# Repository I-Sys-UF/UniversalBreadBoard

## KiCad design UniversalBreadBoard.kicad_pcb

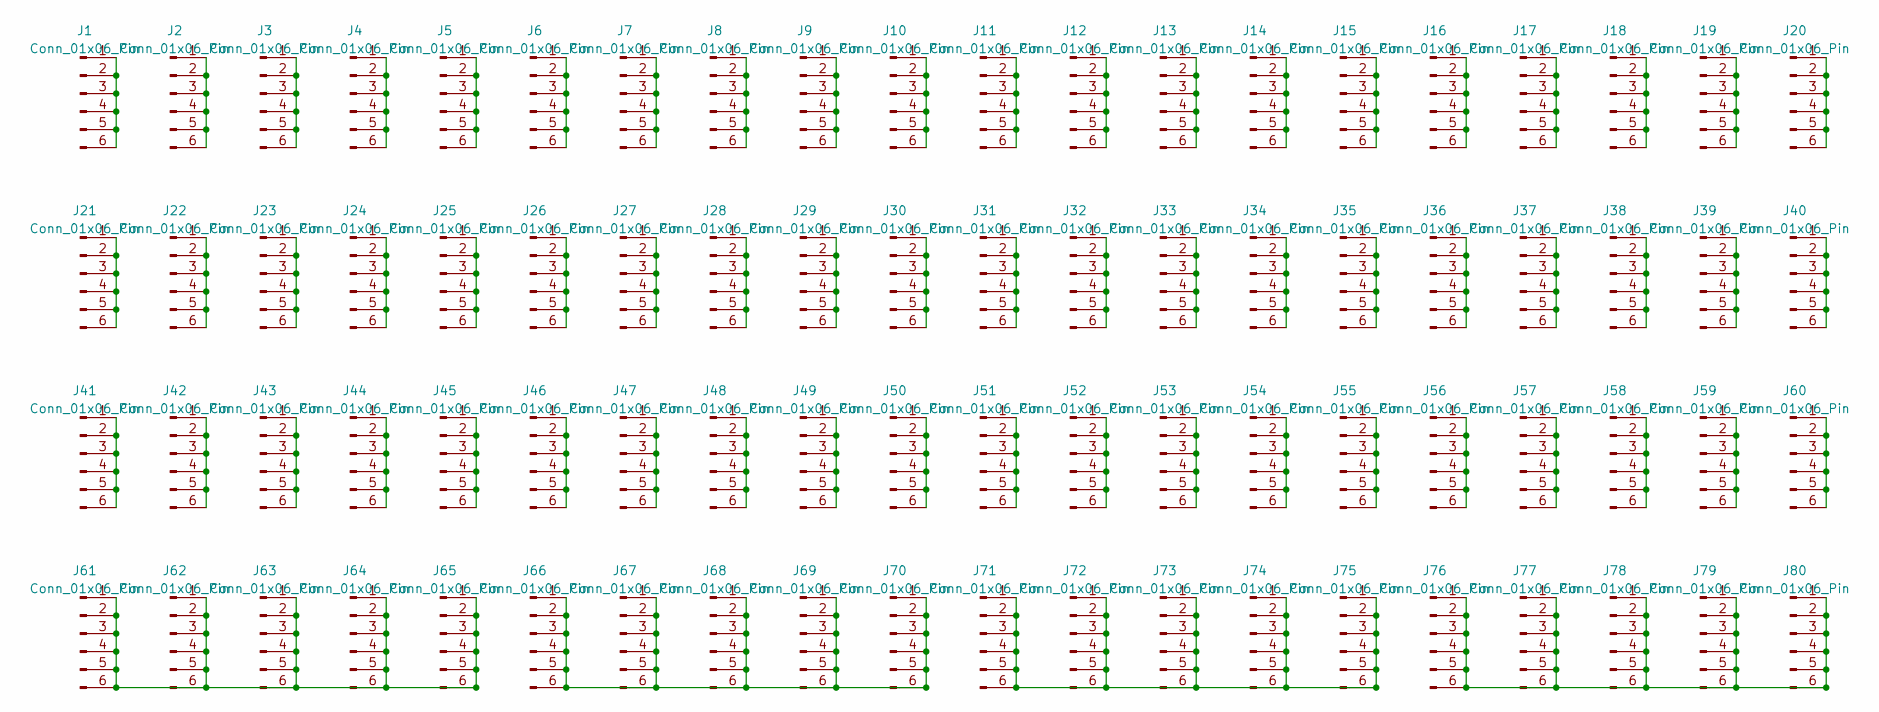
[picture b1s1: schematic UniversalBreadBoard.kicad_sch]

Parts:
J1, J2, J3, J4, J5, J6, J7, J8, J9, J10, J11, J12, J13, J14, J15, J16, J17, J18, J19, J20, J21, J22, J23, J24, J25, J26, J27, J28, J29, J30, J31, J32, J33, J34, J35, J36, J37, J38, J39, J40, J41, J42, J43, J44, J45, J46, J47, J48, J49, J50, J51, J52, J53, J54, J55, J56, J57, J58, J59, J60, J61, J62, J63, J64, J65, J66, J67, J68, J69, J70, J71, J72, J73, J74, J75, J76, J77, J78, J79, J80: Conn_01x06_Pin; Pins

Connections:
unnamed: J1.1, J1.2, J1.3, J1.4, J1.5, J1.6
unnamed: J2.1, J2.2, J2.3, J2.4, J2.5, J2.6
unnamed: J3.1, J3.2, J3.3, J3.4, J3.5, J3.6
unnamed: J4.1, J4.2, J4.3, J4.4, J4.5, J4.6
unnamed: J5.1, J5.2, J5.3, J5.4, J5.5, J5.6
unnamed: J6.1, J6.2, J6.3, J6.4, J6.5, J6.6
unnamed: J7.1, J7.2, J7.3, J7.4, J7.5, J7.6
unnamed: J8.1, J8.2, J8.3, J8.4, J8.5, J8.6
unnamed: J9.1, J9.2, J9.3, J9.4, J9.5, J9.6
unnamed: J10.1, J10.2, J10.3, J10.4, J10.5, J10.6
unnamed: J11.1, J11.2, J11.3, J11.4, J11.5, J11.6
unnamed: J12.1, J12.2, J12.3, J12.4, J12.5, J12.6
unnamed: J13.1, J13.2, J13.3, J13.4, J13.5, J13.6
unnamed: J14.1, J14.2, J14.3, J14.4, J14.5, J14.6
unnamed: J15.1, J15.2, J15.3, J15.4, J15.5, J15.6
unnamed: J16.1, J16.2, J16.3, J16.4, J16.5, J16.6
unnamed: J17.1, J17.2, J17.3, J17.4, J17.5, J17.6
unnamed: J18.1, J18.2, J18.3, J18.4, J18.5, J18.6
unnamed: J19.1, J19.2, J19.3, J19.4, J19.5, J19.6
unnamed: J20.1, J20.2, J20.3, J20.4, J20.5, J20.6
unnamed: J21.1, J21.2, J21.3, J21.4, J21.5, J21.6
unnamed: J22.1, J22.2, J22.3, J22.4, J22.5, J22.6
unnamed: J23.1, J23.2, J23.3, J23.4, J23.5, J23.6
unnamed: J24.1, J24.2, J24.3, J24.4, J24.5, J24.6
unnamed: J25.1, J25.2, J25.3, J25.4, J25.5, J25.6
unnamed: J26.1, J26.2, J26.3, J26.4, J26.5, J26.6
unnamed: J27.1, J27.2, J27.3, J27.4, J27.5, J27.6
unnamed: J28.1, J28.2, J28.3, J28.4, J28.5, J28.6
unnamed: J29.1, J29.2, J29.3, J29.4, J29.5, J29.6
unnamed: J30.1, J30.2, J30.3, J30.4, J30.5, J30.6
unnamed: J31.1, J31.2, J31.3, J31.4, J31.5, J31.6
unnamed: J32.1, J32.2, J32.3, J32.4, J32.5, J32.6
unnamed: J33.1, J33.2, J33.3, J33.4, J33.5, J33.6
unnamed: J34.1, J34.2, J34.3, J34.4, J34.5, J34.6
unnamed: J35.1, J35.2, J35.3, J35.4, J35.5, J35.6
unnamed: J36.1, J36.2, J36.3, J36.4, J36.5, J36.6
unnamed: J37.1, J37.2, J37.3, J37.4, J37.5, J37.6
unnamed: J38.1, J38.2, J38.3, J38.4, J38.5, J38.6
unnamed: J39.1, J39.2, J39.3, J39.4, J39.5, J39.6
unnamed: J40.1, J40.2, J40.3, J40.4, J40.5, J40.6
unnamed: J41.1, J41.2, J41.3, J41.4, J41.5, J41.6
unnamed: J42.1, J42.2, J42.3, J42.4, J42.5, J42.6
unnamed: J43.1, J43.2, J43.3, J43.4, J43.5, J43.6
unnamed: J44.1, J44.2, J44.3, J44.4, J44.5, J44.6
unnamed: J45.1, J45.2, J45.3, J45.4, J45.5, J45.6
unnamed: J46.1, J46.2, J46.3, J46.4, J46.5, J46.6
unnamed: J47.1, J47.2, J47.3, J47.4, J47.5, J47.6
unnamed: J48.1, J48.2, J48.3, J48.4, J48.5, J48.6
unnamed: J49.1, J49.2, J49.3, J49.4, J49.5, J49.6
unnamed: J50.1, J50.2, J50.3, J50.4, J50.5, J50.6
unnamed: J51.1, J51.2, J51.3, J51.4, J51.5, J51.6
unnamed: J52.1, J52.2, J52.3, J52.4, J52.5, J52.6
unnamed: J53.1, J53.2, J53.3, J53.4, J53.5, J53.6
unnamed: J54.1, J54.2, J54.3, J54.4, J54.5, J54.6
unnamed: J55.1, J55.2, J55.3, J55.4, J55.5, J55.6
unnamed: J56.1, J56.2, J56.3, J56.4, J56.5, J56.6
unnamed: J57.1, J57.2, J57.3, J57.4, J57.5, J57.6
unnamed: J58.1, J58.2, J58.3, J58.4, J58.5, J58.6
unnamed: J59.1, J59.2, J59.3, J59.4, J59.5, J59.6
unnamed: J60.1, J60.2, J60.3, J60.4, J60.5, J60.6
unnamed: J61.1, J61.2, J61.3, J61.4, J61.5, J61.6, J62.1, J62.2, J62.3, J62.4, J62.5, J62.6, J63.1, J63.2, J63.3, J63.4, J63.5, J63.6, J64.1, J64.2, J64.3, J64.4, J64.5, J64.6, J65.1, J65.2, J65.3, J65.4, J65.5, J65.6
unnamed: J66.1, J66.2, J66.3, J66.4, J66.5, J66.6, J67.1, J67.2, J67.3, J67.4, J67.5, J67.6, J68.1, J68.2, J68.3, J68.4, J68.5, J68.6, J69.1, J69.2, J69.3, J69.4, J69.5, J69.6, J70.1, J70.2, J70.3, J70.4, J70.5, J70.6
unnamed: J71.1, J71.2, J71.3, J71.4, J71.5, J71.6, J72.1, J72.2, J72.3, J72.4, J72.5, J72.6, J73.1, J73.2, J73.3, J73.4, J73.5, J73.6, J74.1, J74.2, J74.3, J74.4, J74.5, J74.6, J75.1, J75.2, J75.3, J75.4, J75.5, J75.6
unnamed: J76.1, J76.2, J76.3, J76.4, J76.5, J76.6, J77.1, J77.2, J77.3, J77.4, J77.5, J77.6, J78.1, J78.2, J78.3, J78.4, J78.5, J78.6, J79.1, J79.2, J79.3, J79.4, J79.5, J79.6, J80.1, J80.2, J80.3, J80.4, J80.5, J80.6

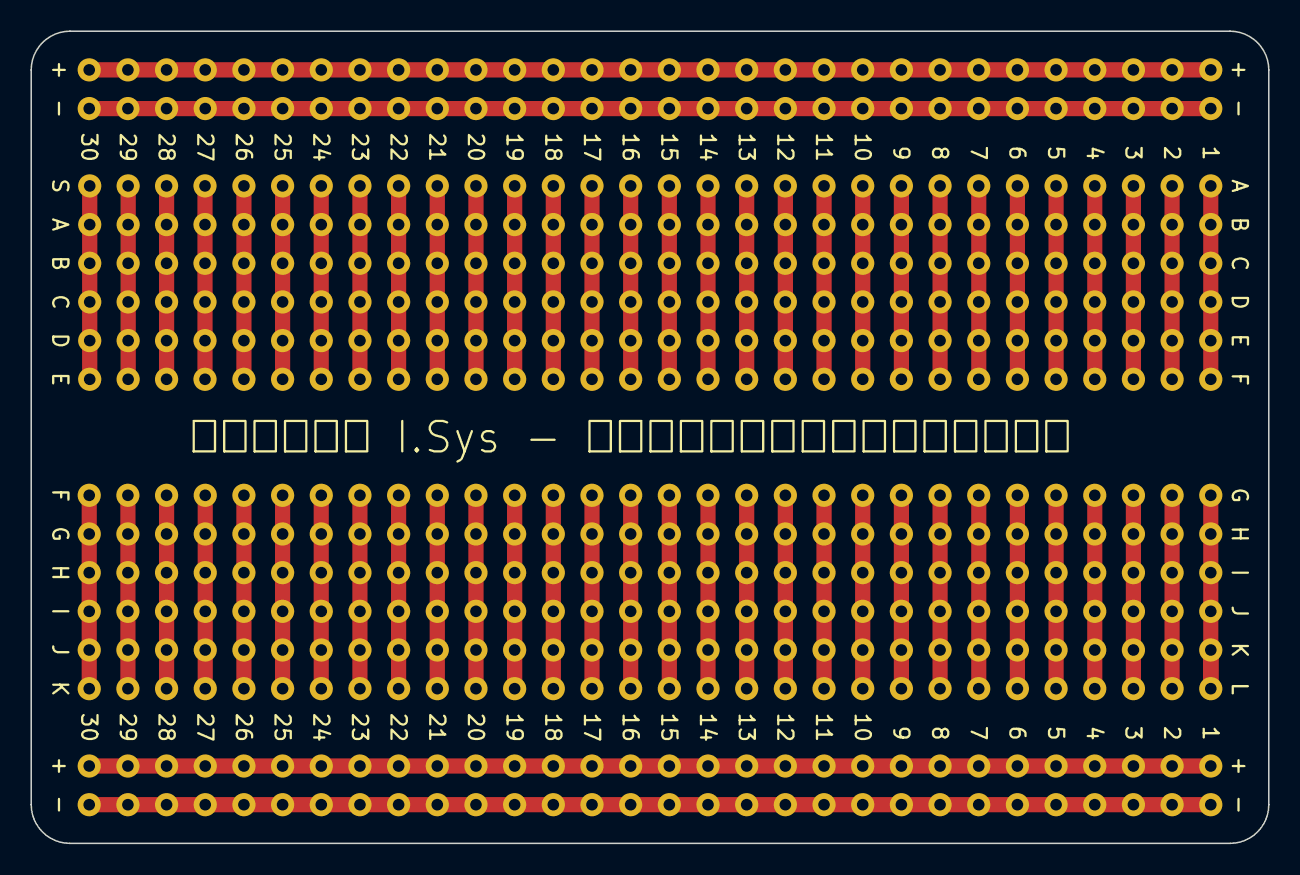
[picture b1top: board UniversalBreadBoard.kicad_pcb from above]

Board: 2 copper layers, 81.3 x 53.3 mm, 80 parts (0 on the bottom side), 64 nets.

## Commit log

2023-11-22 v2 update
    行・列の刻印を追加
2023-11-23 縦方向，中央の刻印を編集
